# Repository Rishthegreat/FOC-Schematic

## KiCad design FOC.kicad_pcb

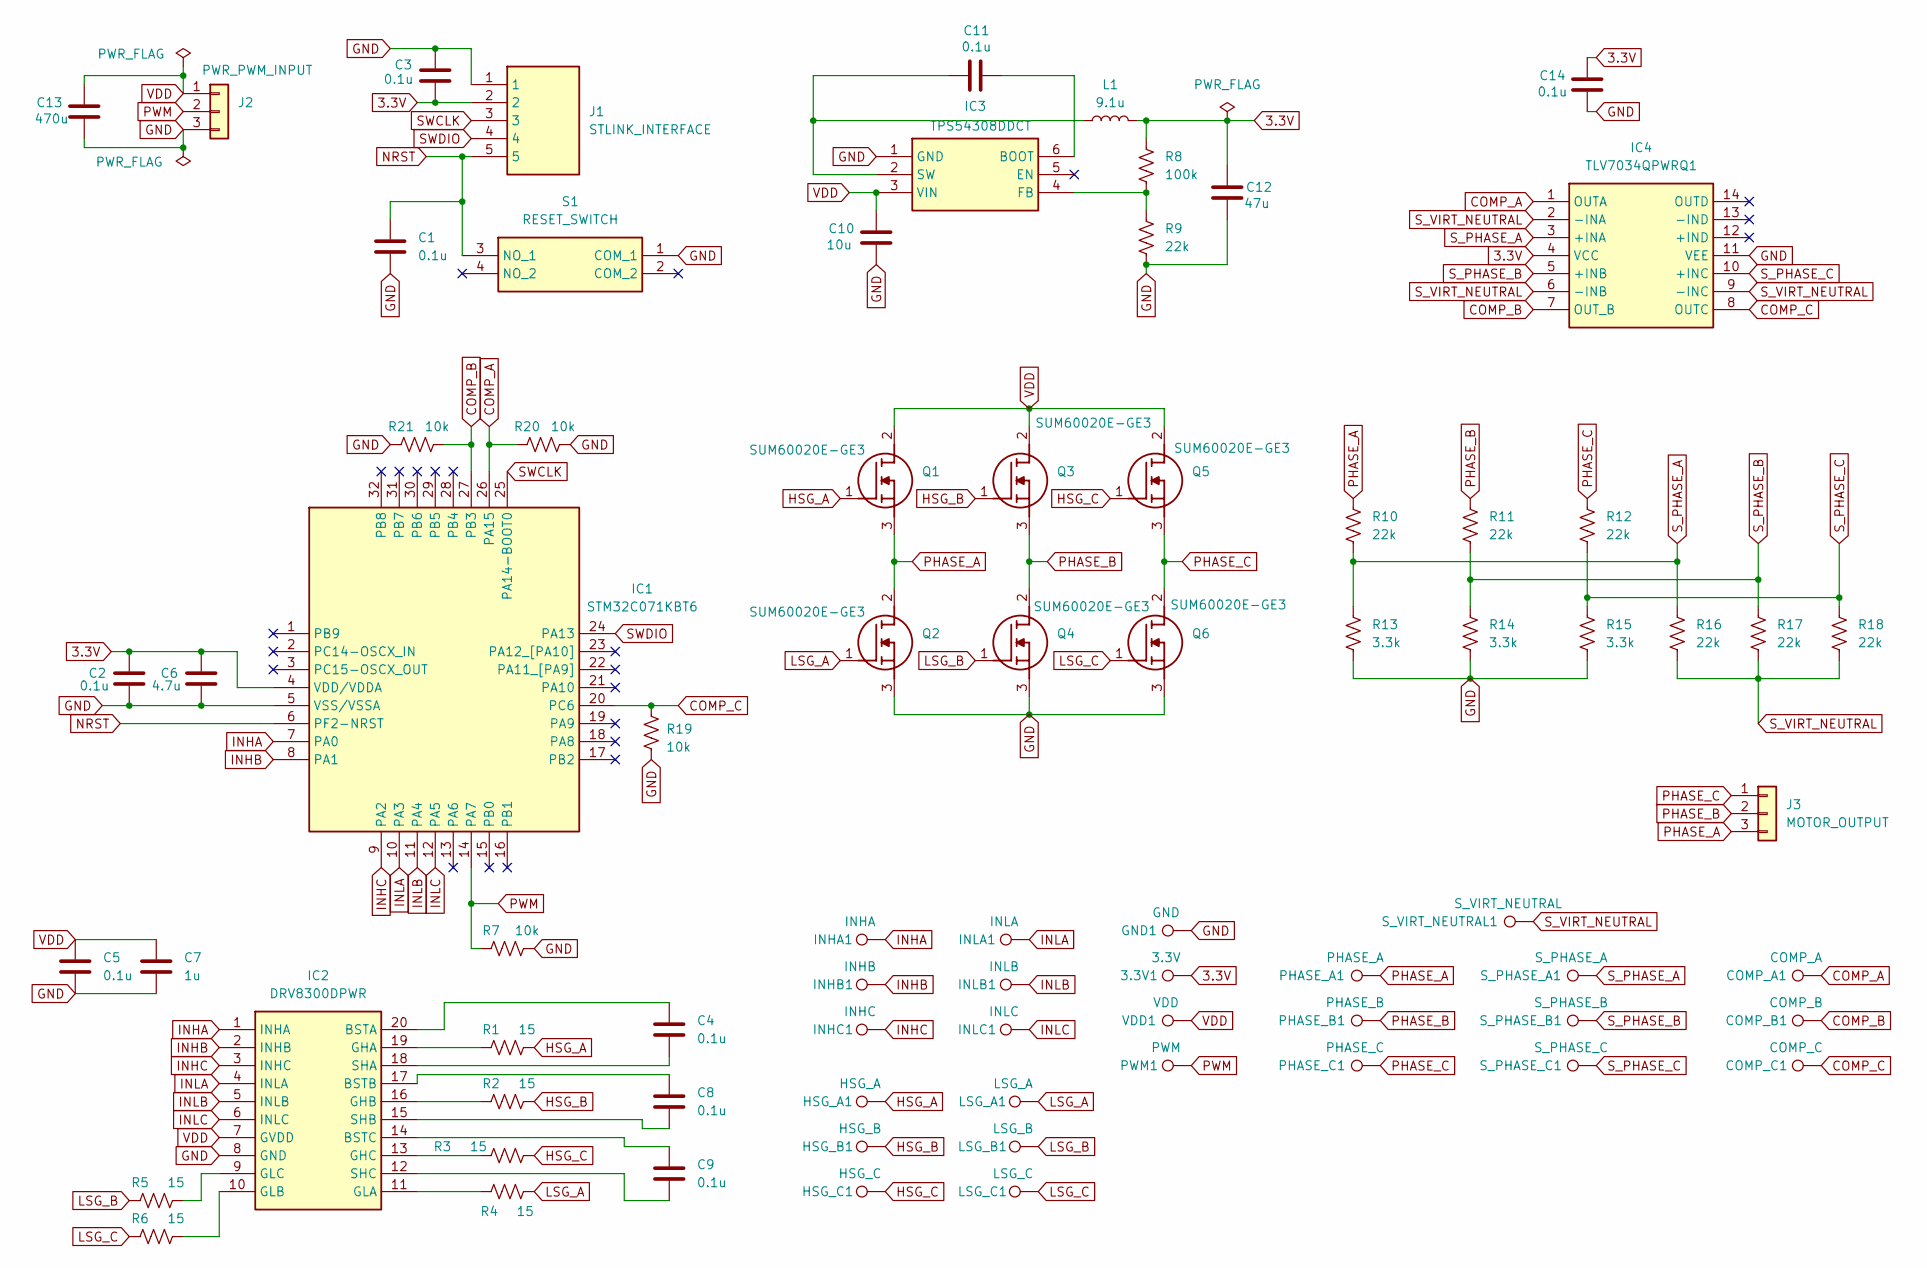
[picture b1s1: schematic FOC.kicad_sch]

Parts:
3.3V1: 3.3V; TestPoint_Keystone_5000-5004_Miniature
C1, C2, C3, C4, C5, C8, C9, C11, C14: 0.1u; C_0805_2012Metric
C6: 4.7u; C_0805_2012Metric
C7: 1u; C_0805_2012Metric
C10: 10u; C_0805_2012Metric
C12: 47u; C_Elec_8x10.2
C13: 470u; C_Radial_D12.5mm_H25.0mm_P5.00mm
COMP_A1: COMP_A; TestPoint_Keystone_5000-5004_Miniature
COMP_B1: COMP_B; TestPoint_Keystone_5000-5004_Miniature
COMP_C1: COMP_C; TestPoint_Keystone_5000-5004_Miniature
GND1: GND; TestPoint_Keystone_5000-5004_Miniature
HSG_A1: HSG_A; TestPoint_Keystone_5000-5004_Miniature
HSG_B1: HSG_B; TestPoint_Keystone_5000-5004_Miniature
HSG_C1: HSG_C; TestPoint_Keystone_5000-5004_Miniature
IC1: STM32C071KBT6; QFP80P900X900X160-32N; Manufacturer_Part_Number STM32C071KBT6
IC2: DRV8300DPWR; SOP65P640X120-20N; Mouser Part Number 595-DRV8300DPWR
IC3: TPS54308DDCT; SOT95P280X110-6N; Mouser Part Number 595-TPS54308DDCT
IC4: TLV7034QPWRQ1; SOP65P640X120-14N; Mouser Part Number 595-TLV7034QPWRQ1
INHA1: INHA; TestPoint_Keystone_5000-5004_Miniature
INHB1: INHB; TestPoint_Keystone_5000-5004_Miniature
INHC1: INHC; TestPoint_Keystone_5000-5004_Miniature
INLA1: INLA; TestPoint_Keystone_5000-5004_Miniature
INLB1: INLB; TestPoint_Keystone_5000-5004_Miniature
INLC1: INLC; TestPoint_Keystone_5000-5004_Miniature
J1: STLINK_INTERFACE; HDRV5W50P0X200_1X5_1000X200X525P; Mouser Part Number 855-M22-2510505
J2: PWR_PWM_INPUT; SolderWire-2.5sqmm_1x03_P7.2mm_D2.4mm_OD3.6mm_Relief
J3: MOTOR_OUTPUT; SolderWire-2.5sqmm_1x03_P7.2mm_D2.4mm_OD3.6mm_Relief
L1: 9.1u; L_Wuerth_WE-PDF
LSG_A1: LSG_A; TestPoint_Keystone_5000-5004_Miniature
LSG_B1: LSG_B; TestPoint_Keystone_5000-5004_Miniature
LSG_C1: LSG_C; TestPoint_Keystone_5000-5004_Miniature
PHASE_A1: PHASE_A; TestPoint_Keystone_5000-5004_Miniature
PHASE_B1: PHASE_B; TestPoint_Keystone_5000-5004_Miniature
PHASE_C1: PHASE_C; TestPoint_Keystone_5000-5004_Miniature
PWM1: PWM; TestPoint_Keystone_5000-5004_Miniature
Q1, Q2, Q3, Q4, Q5, Q6: SUM60020E-GE3; SUM60020EGE3; Mouser Part Number 78-SUM60020E-GE3
R1, R2, R3, R4, R5, R6: 15; R_2512_6332Metric
R7, R19, R20, R21: 10k; R_0805_2012Metric
R8: 100k; R_0805_2012Metric
R9, R10, R11, R12, R16, R17, R18: 22k; R_0805_2012Metric
R13, R14, R15: 3.3k; R_0805_2012Metric
S1: RESET_SWITCH; FSM4JSMATR; Mouser Part Number 506-FSM4JSMAATR
S_PHASE_A1: S_PHASE_A; TestPoint_Keystone_5000-5004_Miniature
S_PHASE_B1: S_PHASE_B; TestPoint_Keystone_5000-5004_Miniature
S_PHASE_C1: S_PHASE_C; TestPoint_Keystone_5000-5004_Miniature
S_VIRT_NEUTRAL1: S_VIRT_NEUTRAL; TestPoint_Keystone_5000-5004_Miniature
VDD1: VDD; TestPoint_Keystone_5000-5004_Miniature

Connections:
3.3V: 3.3V1.1, C2.1, C3.2, C6.1, C12.1, C14.1, IC1.4 (VDD/VDDA), IC4.4 (VCC), J1.2, L1.2, R8.1
COMP_A: COMP_A1.1, IC1.26 (PA15), IC4.1 (OUTA), R20.1
COMP_B: COMP_B1.1, IC1.27 (PB3), IC4.7 (OUT_B), R21.2
COMP_C: COMP_C1.1, IC1.20 (PC6), IC4.8 (OUTC), R19.1
GND: C1.2, C2.2, C3.1, C5.2, C6.2, C7.2, C10.2, C12.2, C13.2, C14.2, GND1.1, IC1.5 (VSS/VSSA), IC2.8 (GND), IC3.1 (GND), IC4.11 (VEE), J1.1, J2.3, Q2.3 (S), Q4.3 (S), Q6.3 (S), R7.2, R9.2, R13.2, R14.2, R15.2, R19.2, R20.2, R21.1, S1.1 (COM_1)
HSG_A: HSG_A1.1, Q1.1 (G), R1.2
HSG_B: HSG_B1.1, Q3.1 (G), R2.2
HSG_C: HSG_C1.1, Q5.1 (G), R3.2
INHA: IC1.7 (PA0), IC2.1 (INHA), INHA1.1
INHB: IC1.8 (PA1), IC2.2 (INHB), INHB1.1
INHC: IC1.9 (PA2), IC2.3 (INHC), INHC1.1
INLA: IC1.10 (PA3), IC2.4 (INLA), INLA1.1
INLB: IC1.11 (PA4), IC2.5 (INLB), INLB1.1
INLC: IC1.12 (PA5), IC2.6 (INLC), INLC1.1
LSG_A: LSG_A1.1, Q2.1 (G), R4.2
LSG_B: LSG_B1.1, Q4.1 (G), R5.1
LSG_C: LSG_C1.1, Q6.1 (G), R6.1
NRST: C1.1, IC1.6 (PF2-NRST), J1.5, S1.3 (NO_1)
unnamed: C4.1, IC2.20 (BSTA)
unnamed: C8.1, IC2.17 (BSTB)
unnamed: C9.1, IC2.14 (BSTC)
unnamed: IC2.19 (GHA), R1.1
unnamed: IC2.16 (GHB), R2.1
unnamed: IC2.13 (GHC), R3.1
unnamed: IC2.11 (GLA), R4.1
unnamed: IC2.10 (GLB), R6.2
unnamed: IC2.9 (GLC), R5.2
unnamed: C4.2, IC2.18 (SHA)
unnamed: C8.2, IC2.15 (SHB)
unnamed: C9.2, IC2.12 (SHC)
unnamed: C11.1, IC3.6 (BOOT)
unnamed: IC3.4 (FB), R8.2, R9.1
unnamed: C11.2, IC3.2 (SW), L1.1
PHASE_A: J3.3, PHASE_A1.1, Q1.3 (S), Q2.2 (D), R10.1
PHASE_B: J3.2, PHASE_B1.1, Q3.3 (S), Q4.2 (D), R11.1
PHASE_C: J3.1, PHASE_C1.1, Q5.3 (S), Q6.2 (D), R12.1
PWM: IC1.14 (PA7), J2.2, PWM1.1, R7.1
SWCLK: IC1.25 (PA14-BOOT0), J1.3
SWDIO: IC1.24 (PA13), J1.4
S_PHASE_A: IC4.3 (+INA), R10.2, R13.1, R16.1, S_PHASE_A1.1
S_PHASE_B: IC4.5 (+INB), R11.2, R14.1, R17.1, S_PHASE_B1.1
S_PHASE_C: IC4.10 (+INC), R12.2, R15.1, R18.1, S_PHASE_C1.1
S_VIRT_NEUTRAL: IC4.2 (-INA), IC4.6 (-INB), IC4.9 (-INC), R16.2, R17.2, R18.2, S_VIRT_NEUTRAL1.1
VDD: C5.1, C7.1, C10.1, C13.1, IC2.7 (GVDD), IC3.3 (VIN), J2.1, Q1.2 (D), Q3.2 (D), Q5.2 (D), VDD1.1

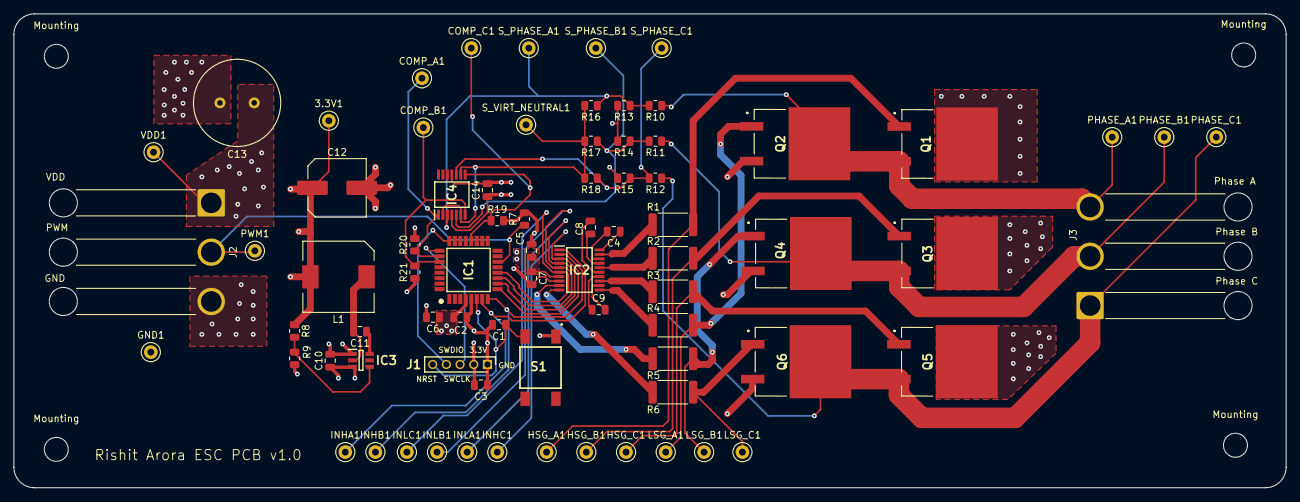
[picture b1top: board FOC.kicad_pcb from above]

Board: 4 copper layers, 185.8 x 69.2 mm, 80 parts (0 on the bottom side), 44 nets.

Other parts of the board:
Mounting: MountingHole_3.5mm
Mounting#2, Mounting#3, Mounting#4: MountingHole_3.5mm

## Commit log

2025-01-07 Final Push
2025-02-20 V1.0 Final
